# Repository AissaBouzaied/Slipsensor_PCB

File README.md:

# Slipsensor_PCB
Small and simple PCB that gives 5V and 12V power to our slipsensor which measures the speed of the car and yaw rate. These measurments go through some signal processing in the pcb then to the ECU. This PCB was done as prototype solution to test our slipsensor and the signal processing(analog and digital).

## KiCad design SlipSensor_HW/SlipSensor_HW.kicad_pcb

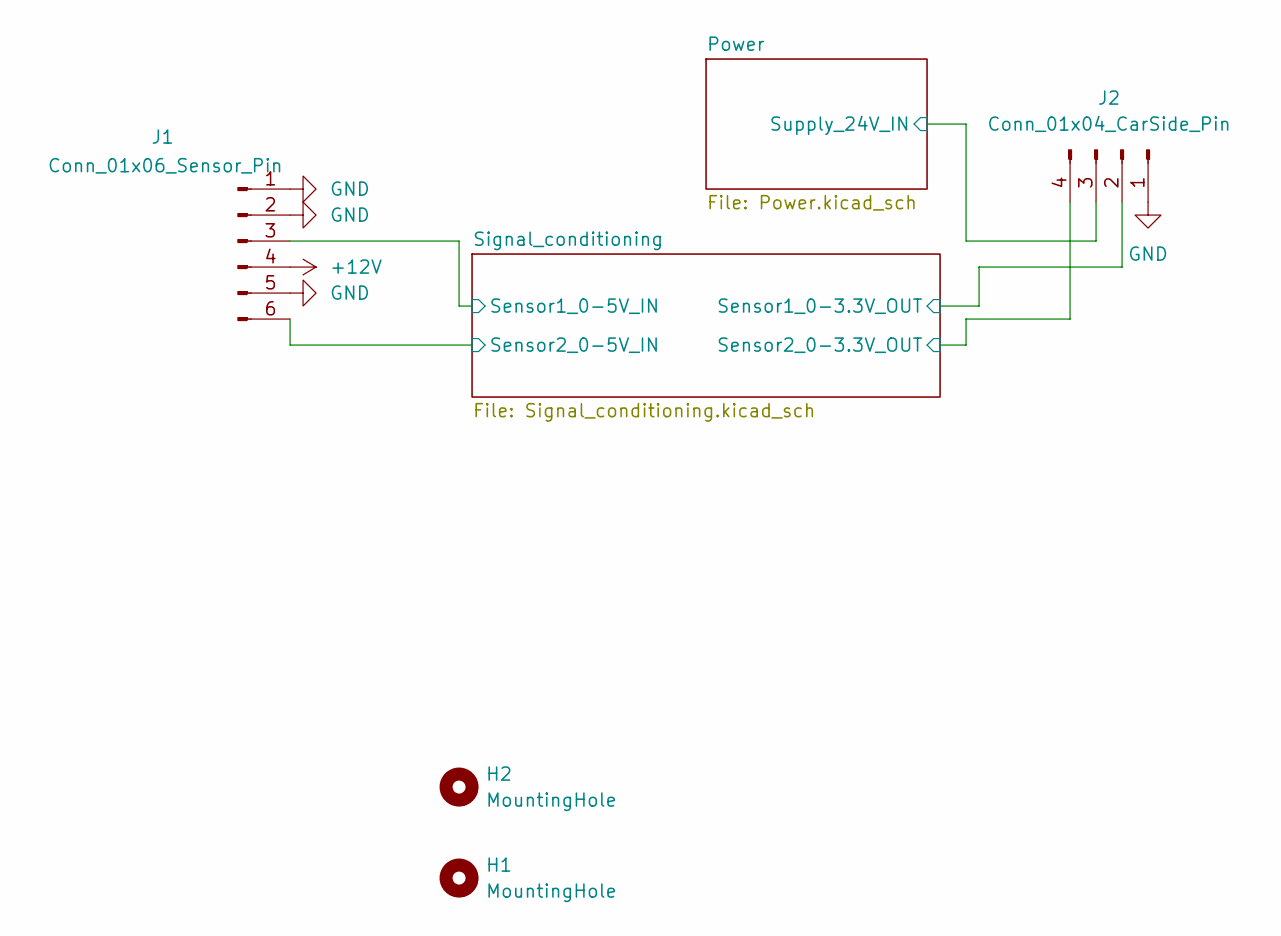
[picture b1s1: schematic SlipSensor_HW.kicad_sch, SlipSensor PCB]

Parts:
H1, H2: MountingHole; MountingHole_3.2mm_M3
J1: Conn_01x06_Sensor_Pin; Wurth-MPC3_02x03_angle
J2: Conn_01x04_CarSide_Pin; Wurth-MPC3_02x02_angle

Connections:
+12V: J1.4; also elsewhere on the board
/Power/Supply_24V_IN: J2.3; also elsewhere on the board
/Signal_conditioning/Sensor1_0-3.3V_OUT: J2.2; also elsewhere on the board
/Signal_conditioning/Sensor1_0-5V_IN: J1.3; also elsewhere on the board
/Signal_conditioning/Sensor2_0-3.3V_OUT: J2.4; also elsewhere on the board
/Signal_conditioning/Sensor2_0-5V_IN: J1.6; also elsewhere on the board
GND: J1.1, J1.2, J1.5, J2.1; also elsewhere on the board

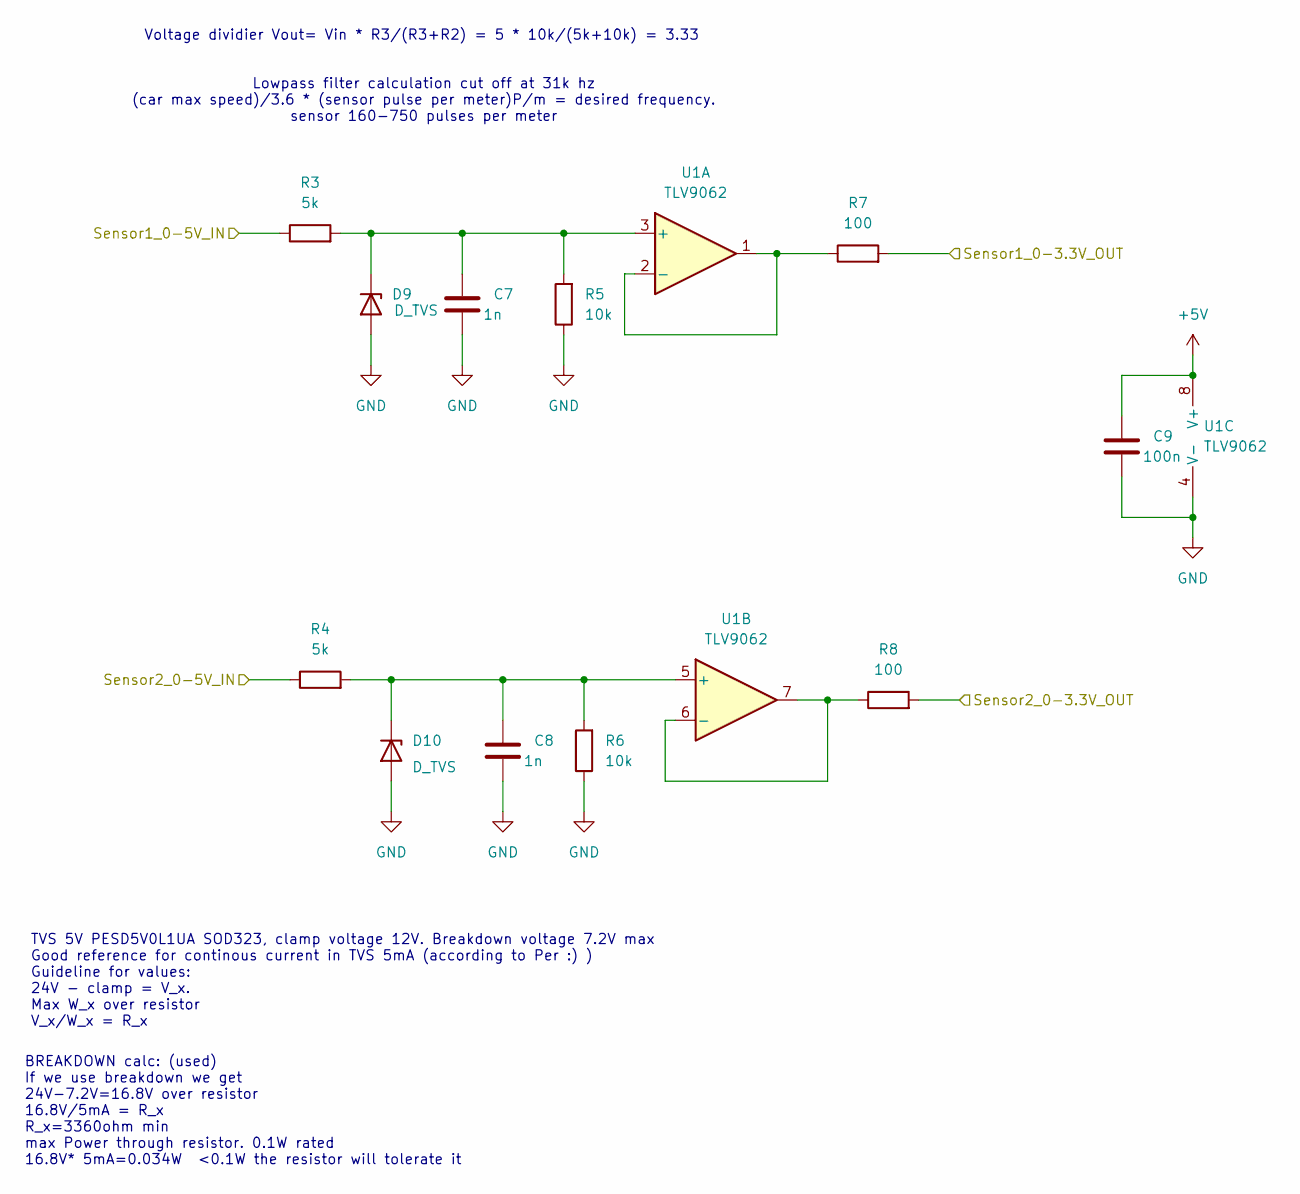
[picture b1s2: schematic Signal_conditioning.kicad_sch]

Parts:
C7, C8: 1n; C_0603_1608Metric
C9: 100n; C_0603_1608Metric
D9, D10: D_TVS; D_SOD-323_HandSoldering
R3, R4: 5k; R_0603_1608Metric
R5, R6: 10k; R_0603_1608Metric
R7, R8: 100; R_0603_1608Metric
U1: TLV9062; SOIC-8_3.9x4.9mm_P1.27mm

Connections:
+5V: C9.1, U1.8 (V+); also elsewhere on the board
/Signal_conditioning/Sensor1_0-3.3V_OUT: R7.2; also elsewhere on the board
/Signal_conditioning/Sensor1_0-5V_IN: R3.1; also elsewhere on the board
/Signal_conditioning/Sensor2_0-3.3V_OUT: R8.2; also elsewhere on the board
/Signal_conditioning/Sensor2_0-5V_IN: R4.1; also elsewhere on the board
GND: C7.2, C8.2, C9.2, D9.2 (A), D10.2 (A), R5.1, R6.1, U1.4 (V-); also elsewhere on the board
unnamed: C7.1, D9.1 (K), R3.2, R5.2, U1.3 (+)
unnamed: C8.1, D10.1 (K), R4.2, R6.2, U1.5 (+)
unnamed: R7.1, U1.1, U1.2 (-)
unnamed: R8.1, U1.6 (-), U1.7

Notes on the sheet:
TVS 5V PESD5V0L1UA SOD323, clamp voltage 12V. Breakdown voltage 7.2V max Good reference for continous current in TVS 5mA (according to Per :) ) Guideline for values: 24V - clamp = V_x. Max W_x over resistor V_x/W_x = R_x
Lowpass filter calculation cut off at 31k hz (car max speed)/3.6 * (sensor pulse per meter)P/m = desired frequency. sensor 160-750 pulses per meter
BREAKDOWN calc: (used) If we use breakdown we get 24V-7.2V=16.8V over resistor 16.8V/5mA = R_x R_x=3360ohm min max Power through resistor. 0.1W rated 16.8V* 5mA=0.034W <0.1W the resistor will tolerate it
Voltage dividier Vout= Vin * R3/(R3+R2) = 5 * 10k/(5k+10k) = 3.33

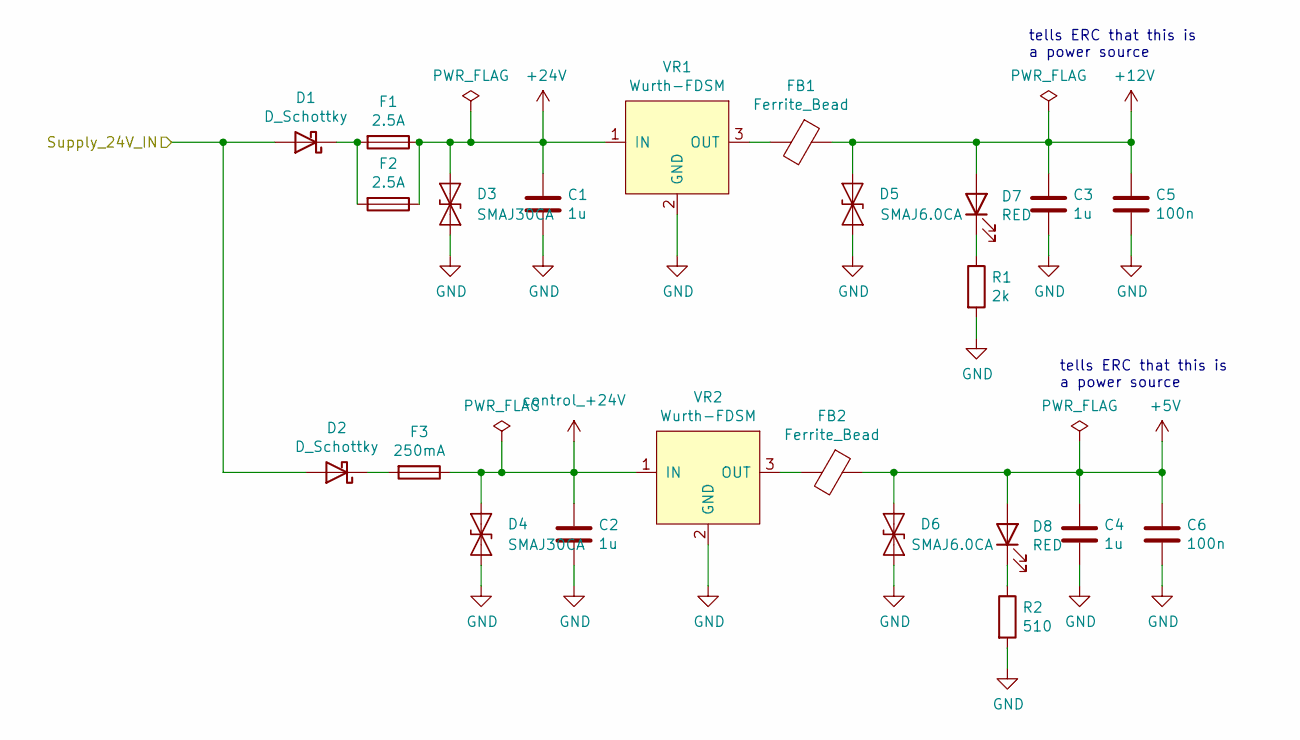
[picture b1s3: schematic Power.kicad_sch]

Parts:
C1, C2, C3, C4: 1u; C_0603_1608Metric_Pad1.08x0.95mm_HandSolder
C5, C6: 100n; C_0603_1608Metric_Pad1.08x0.95mm_HandSolder
D1, D2: D_Schottky; D_SOD-323_HandSoldering
D3, D4: SMAJ30CA; D_SOD-323_HandSoldering
D5, D6: SMAJ6.0CA; D_SOD-323_HandSoldering
D7, D8: RED; LED_0603_1608Metric_Pad1.05x0.95mm_HandSolder
F1, F2: 2.5A; Fuse_0805_2012Metric_Pad1.15x1.40mm_HandSolder
F3: 250mA; Fuse_0805_2012Metric_Pad1.15x1.40mm_HandSolder
FB1, FB2: Ferrite_Bead; L_0603_1608Metric_Pad1.05x0.95mm_HandSolder
R1: 2k; R_0603_1608Metric_Pad0.98x0.95mm_HandSolder
R2: 510; R_0603_1608Metric_Pad0.98x0.95mm_HandSolder
VR1, VR2: Wurth-FDSM

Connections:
+5V: C4.1, C6.1, D6.1 (A1), D8.2 (A), FB2.1; also elsewhere on the board
+12V: C3.1, C5.1, D5.1 (A1), D7.2 (A), FB1.1; also elsewhere on the board
+24V: C1.1, D3.1 (A1), F1.1, F2.1, VR1.1 (IN)
/Power/Supply_24V_IN: D1.2 (A), D2.2 (A); also elsewhere on the board
GND: C1.2, C2.2, C3.2, C4.2, C5.2, C6.2, D3.2 (A2), D4.2 (A2), D5.2 (A2), D6.2 (A2), R1.2, R2.2, VR1.2 (GND), VR2.2 (GND); also elsewhere on the board
unnamed: D1.1 (K), F1.2, F2.2
unnamed: D2.1 (K), F3.2
unnamed: D7.1 (K), R1.1
unnamed: D8.1 (K), R2.1
unnamed: FB1.2, VR1.3 (OUT)
unnamed: FB2.2, VR2.3 (OUT)
control_+24V: C2.1, D4.1 (A1), F3.1, VR2.1 (IN)

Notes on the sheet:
tells ERC that this is a power source

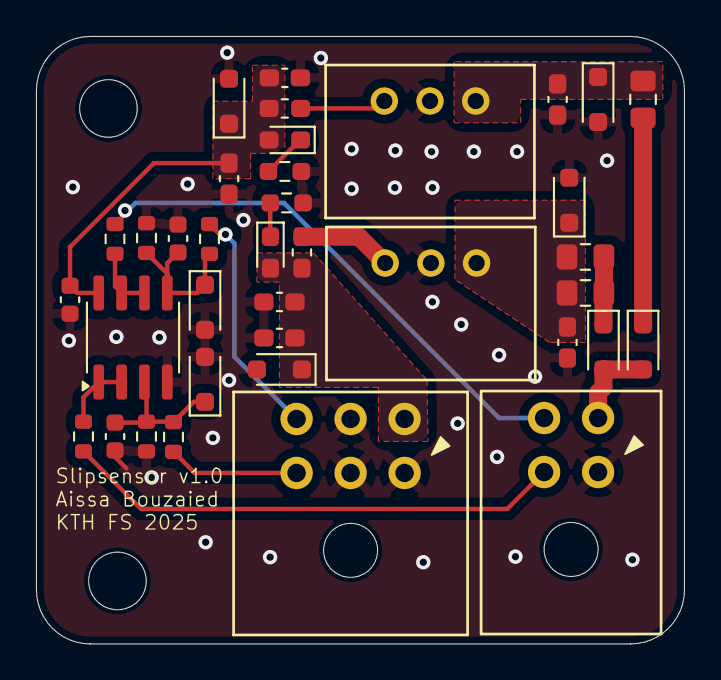
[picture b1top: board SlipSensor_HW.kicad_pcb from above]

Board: 2 copper layers, 36.0 x 33.8 mm, 39 parts (0 on the bottom side), 20 nets.
